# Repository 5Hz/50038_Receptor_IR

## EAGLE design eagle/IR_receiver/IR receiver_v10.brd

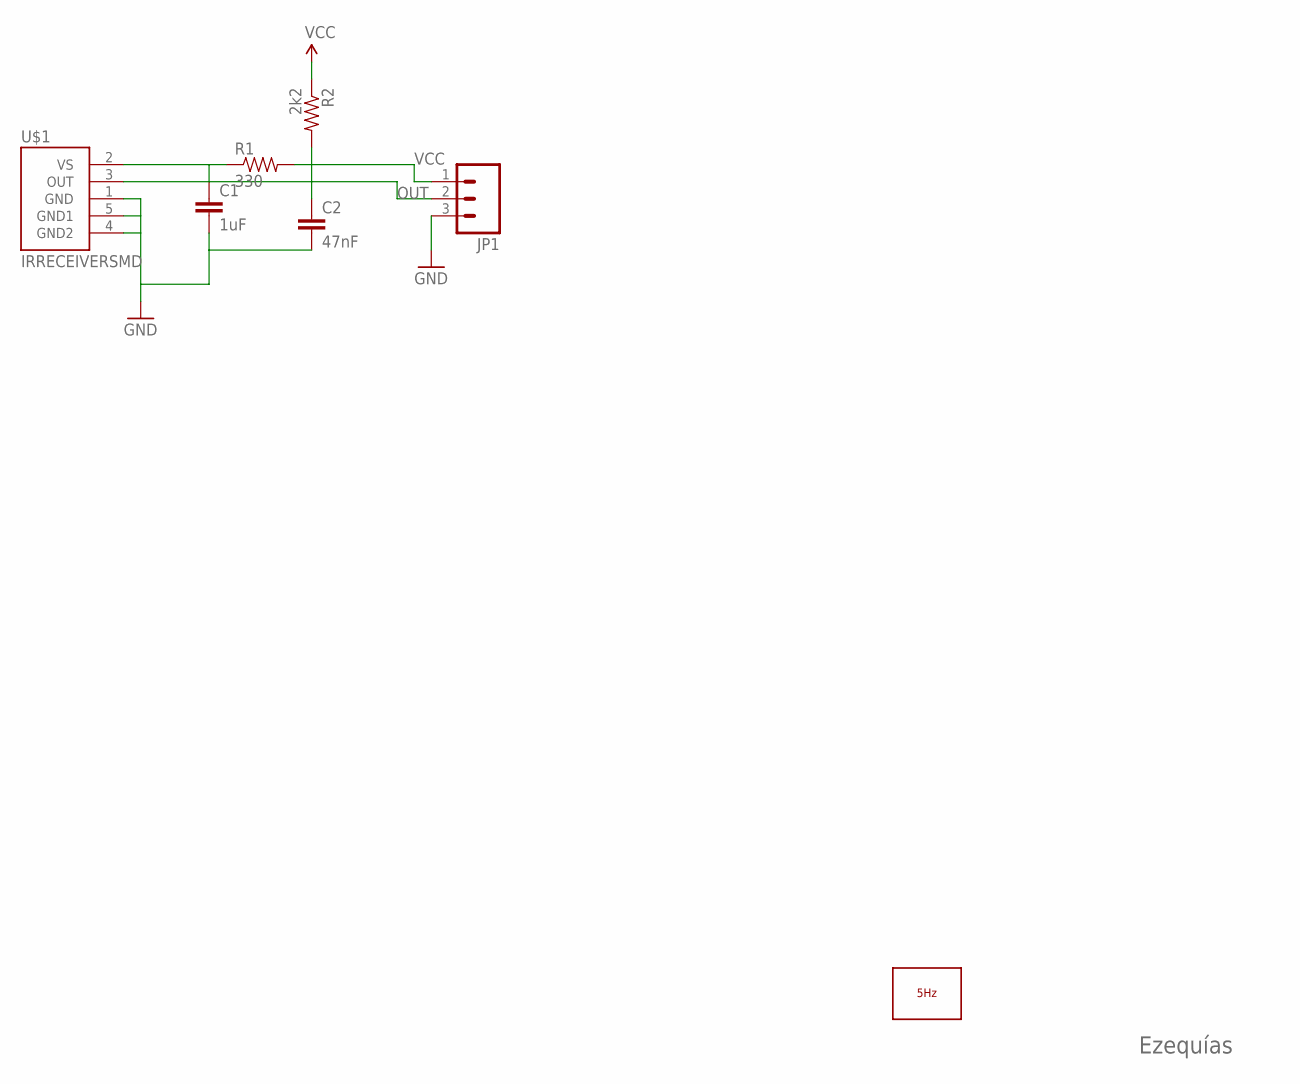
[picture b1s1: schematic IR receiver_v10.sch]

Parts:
C1: 1uF; 0603-CAP
C2: 47nF; 0603-CAP
JP1: M03PTH; 1X03
LOGO1: LOGO_5HZ_MAIN_5MM; 5HZ_LOGO_MAIN_5MM
R1: 330; 0603-RES
R2: 2k2; 0603-RES
U$1: IRRECEIVERSMD; TSOP8523

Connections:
GND: C1.2, C2.2, JP1.3, U$1.1 (GND), U$1.4 (GND2), U$1.5 (GND1)
unnamed: C1.1, R1.1, U$1.2 (VS)
OUT: C2.1, JP1.2, R2.2, U$1.3 (OUT)
VCC: JP1.1, R1.2, R2.1

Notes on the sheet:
Ezequías

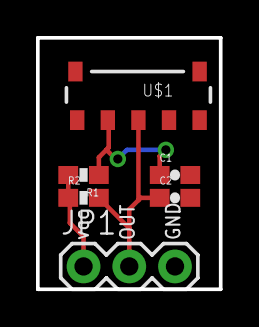
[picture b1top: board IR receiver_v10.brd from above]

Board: 2 copper layers, 10.2 x 14.0 mm, 7 parts (1 on the bottom side), 4 nets.

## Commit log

2014-01-10 creación
